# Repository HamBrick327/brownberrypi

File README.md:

# brownberrypi
my cyberdeck project and my first try at PCB design.

## note: the keyboard is not perfectly square, I did a dumb and only eyeballed it in KiCad, fix reccomended

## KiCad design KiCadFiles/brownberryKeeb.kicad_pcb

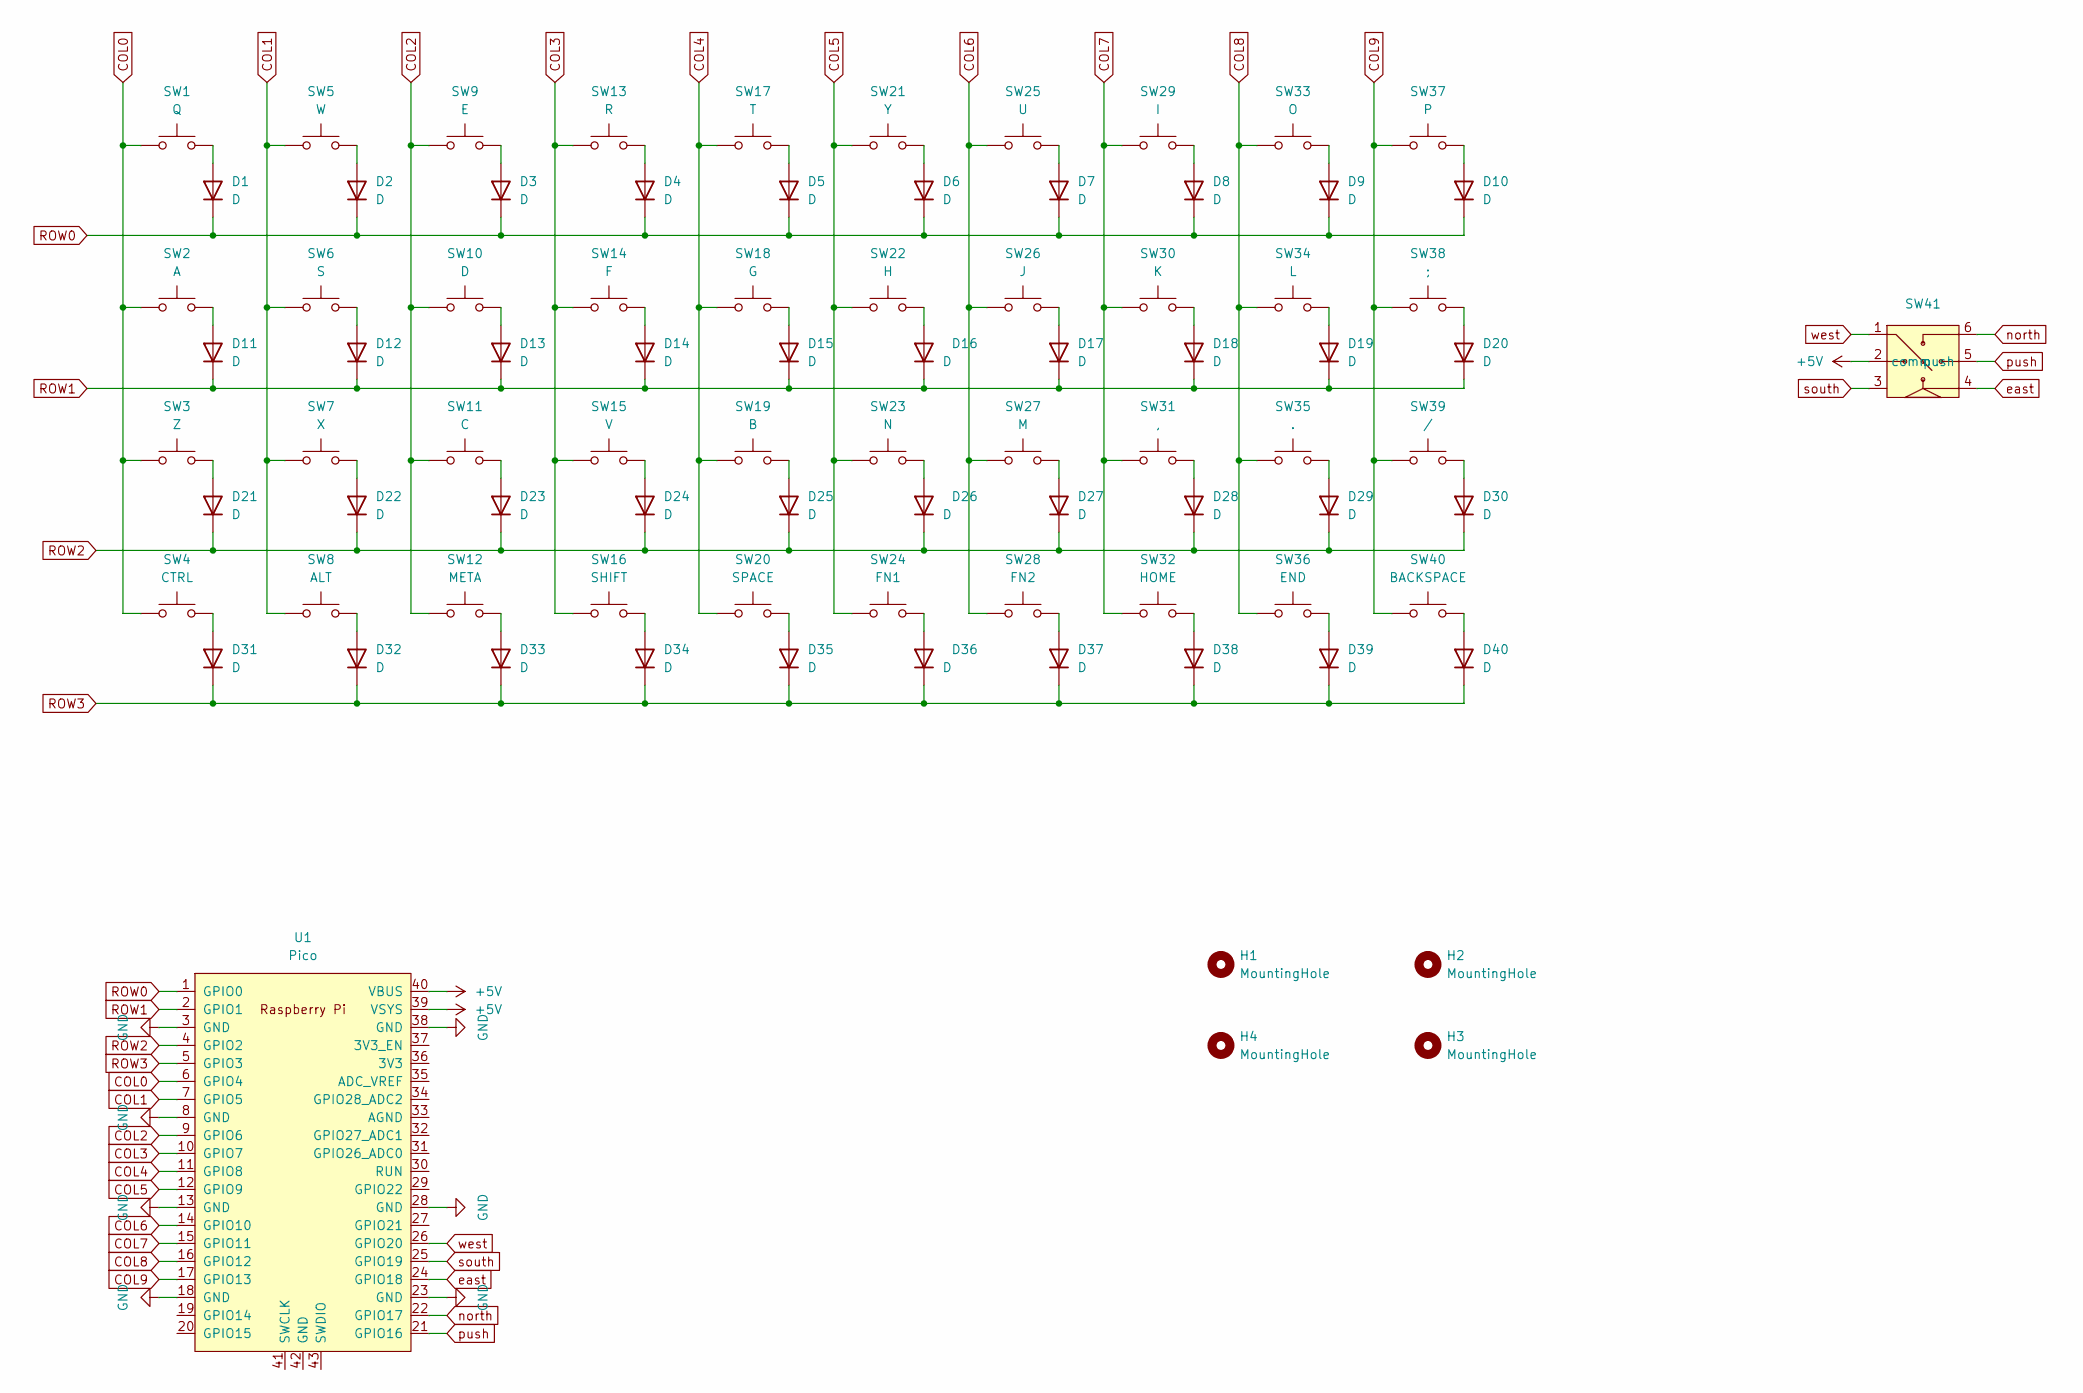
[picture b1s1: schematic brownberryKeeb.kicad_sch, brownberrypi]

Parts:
D1, D2, D3, D4, D5, D6, D7, D8, D9, D10, D11, D12, D13, D14, D15, D16, D17, D18, D19, D20, D21, D22, D23, D24, D25, D26, D27, D28, D29, D30, D31, D32, D33, D34, D35, D36, D37, D38, D39, D40: D; D_SOD-123
H1, H2, H3, H4: MountingHole; MountingHole_2.1mm
SW1: Q; SW_Push_1P1T_XKB_TS-1187A
SW2: A; SW_Push_1P1T_XKB_TS-1187A
SW3: Z; SW_Push_1P1T_XKB_TS-1187A
SW4: CTRL; SW_Push_1P1T_XKB_TS-1187A
SW5: W; SW_Push_1P1T_XKB_TS-1187A
SW6: S; SW_Push_1P1T_XKB_TS-1187A
SW7: X; SW_Push_1P1T_XKB_TS-1187A
SW8: ALT; SW_Push_1P1T_XKB_TS-1187A
SW9: E; SW_Push_1P1T_XKB_TS-1187A
SW10: D; SW_Push_1P1T_XKB_TS-1187A
SW11: C; SW_Push_1P1T_XKB_TS-1187A
SW12: META; SW_Push_1P1T_XKB_TS-1187A
SW13: R; SW_Push_1P1T_XKB_TS-1187A
SW14: F; SW_Push_1P1T_XKB_TS-1187A
SW15: V; SW_Push_1P1T_XKB_TS-1187A
SW16: SHIFT; SW_Push_1P1T_XKB_TS-1187A
SW17: T; SW_Push_1P1T_XKB_TS-1187A
SW18: G; SW_Push_1P1T_XKB_TS-1187A
SW19: B; SW_Push_1P1T_XKB_TS-1187A
SW20: SPACE; SW_Push_1P1T_XKB_TS-1187A
SW21: Y; SW_Push_1P1T_XKB_TS-1187A
SW22: H; SW_Push_1P1T_XKB_TS-1187A
SW23: N; SW_Push_1P1T_XKB_TS-1187A
SW24: FN1; SW_Push_1P1T_XKB_TS-1187A
SW25: U; SW_Push_1P1T_XKB_TS-1187A
SW26: J; SW_Push_1P1T_XKB_TS-1187A
SW27: M; SW_Push_1P1T_XKB_TS-1187A
SW28: FN2; SW_Push_1P1T_XKB_TS-1187A
SW29: I; SW_Push_1P1T_XKB_TS-1187A
SW30: K; SW_Push_1P1T_XKB_TS-1187A
SW31: ,; SW_Push_1P1T_XKB_TS-1187A
SW32: HOME; SW_Push_1P1T_XKB_TS-1187A
SW33: O; SW_Push_1P1T_XKB_TS-1187A
SW34: L; SW_Push_1P1T_XKB_TS-1187A
SW35: .; SW_Push_1P1T_XKB_TS-1187A
SW36: END; SW_Push_1P1T_XKB_TS-1187A
SW37: P; SW_Push_1P1T_XKB_TS-1187A
SW38: ;; SW_Push_1P1T_XKB_TS-1187A
SW39: /; SW_Push_1P1T_XKB_TS-1187A
SW40: BACKSPACE; SW_Push_1P1T_XKB_TS-1187A
SW41: 7x7x5_5-way_switch
U1: Pico; RaspberryPi_Pico_SMD

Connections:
+5V: SW41.2 (comm), U1.39 (VSYS), U1.40 (VBUS)
COL0: SW1.1, SW2.1, SW3.1, SW4.1, U1.6 (GPIO4)
COL1: SW5.1, SW6.1, SW7.1, SW8.1, U1.7 (GPIO5)
COL2: SW9.1, SW10.1, SW11.1, SW12.1, U1.9 (GPIO6)
COL3: SW13.1, SW14.1, SW15.1, SW16.1, U1.10 (GPIO7)
COL4: SW17.1, SW18.1, SW19.1, SW20.1, U1.11 (GPIO8)
COL5: SW21.1, SW22.1, SW23.1, SW24.1, U1.12 (GPIO9)
COL6: SW25.1, SW26.1, SW27.1, SW28.1, U1.14 (GPIO10)
COL7: SW29.1, SW30.1, SW31.1, SW32.1, U1.15 (GPIO11)
COL8: SW33.1, SW34.1, SW35.1, SW36.1, U1.16 (GPIO12)
COL9: SW37.1, SW38.1, SW39.1, SW40.1, U1.17 (GPIO13)
GND: U1.3 (GND), U1.8 (GND), U1.13 (GND), U1.18 (GND), U1.23 (GND), U1.28 (GND), U1.38 (GND)
unnamed: D1.2 (A), SW1.2
unnamed: D2.2 (A), SW5.2
unnamed: D3.2 (A), SW9.2
unnamed: D4.2 (A), SW13.2
unnamed: D5.2 (A), SW17.2
unnamed: D6.2 (A), SW21.2
unnamed: D7.2 (A), SW25.2
unnamed: D8.2 (A), SW29.2
unnamed: D9.2 (A), SW33.2
unnamed: D10.2 (A), SW37.2
unnamed: D11.2 (A), SW2.2
unnamed: D12.2 (A), SW6.2
unnamed: D13.2 (A), SW10.2
unnamed: D14.2 (A), SW14.2
unnamed: D15.2 (A), SW18.2
unnamed: D16.2 (A), SW22.2
unnamed: D17.2 (A), SW26.2
unnamed: D18.2 (A), SW30.2
unnamed: D19.2 (A), SW34.2
unnamed: D20.2 (A), SW38.2
unnamed: D21.2 (A), SW3.2
unnamed: D22.2 (A), SW7.2
unnamed: D23.2 (A), SW11.2
unnamed: D24.2 (A), SW15.2
unnamed: D25.2 (A), SW19.2
unnamed: D26.2 (A), SW23.2
unnamed: D27.2 (A), SW27.2
unnamed: D28.2 (A), SW31.2
unnamed: D29.2 (A), SW35.2
unnamed: D30.2 (A), SW39.2
unnamed: D31.2 (A), SW4.2
unnamed: D32.2 (A), SW8.2
unnamed: D33.2 (A), SW12.2
unnamed: D34.2 (A), SW16.2
unnamed: D35.2 (A), SW20.2
unnamed: D36.2 (A), SW24.2
unnamed: D37.2 (A), SW28.2
unnamed: D38.2 (A), SW32.2
unnamed: D39.2 (A), SW36.2
unnamed: D40.2 (A), SW40.2
ROW0: D1.1 (K), D2.1 (K), D3.1 (K), D4.1 (K), D5.1 (K), D6.1 (K), D7.1 (K), D8.1 (K), D9.1 (K), D10.1 (K), U1.1 (GPIO0)
ROW1: D11.1 (K), D12.1 (K), D13.1 (K), D14.1 (K), D15.1 (K), D16.1 (K), D17.1 (K), D18.1 (K), D19.1 (K), D20.1 (K), U1.2 (GPIO1)
ROW2: D21.1 (K), D22.1 (K), D23.1 (K), D24.1 (K), D25.1 (K), D26.1 (K), D27.1 (K), D28.1 (K), D29.1 (K), D30.1 (K), U1.4 (GPIO2)
ROW3: D31.1 (K), D32.1 (K), D33.1 (K), D34.1 (K), D35.1 (K), D36.1 (K), D37.1 (K), D38.1 (K), D39.1 (K), D40.1 (K), U1.5 (GPIO3)
east: SW41.4, U1.24 (GPIO18)
north: SW41.6, U1.22 (GPIO17)
push: SW41.5 (push), U1.21 (GPIO16)
south: SW41.3, U1.25 (GPIO19)
west: SW41.1, U1.26 (GPIO20)

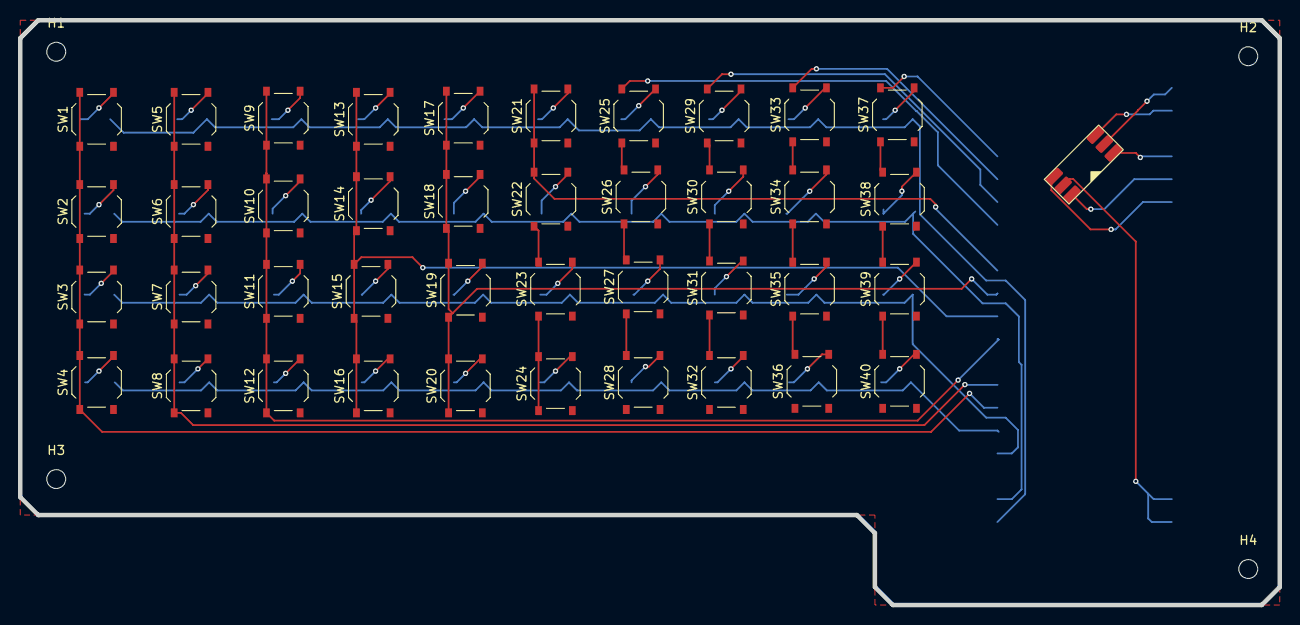
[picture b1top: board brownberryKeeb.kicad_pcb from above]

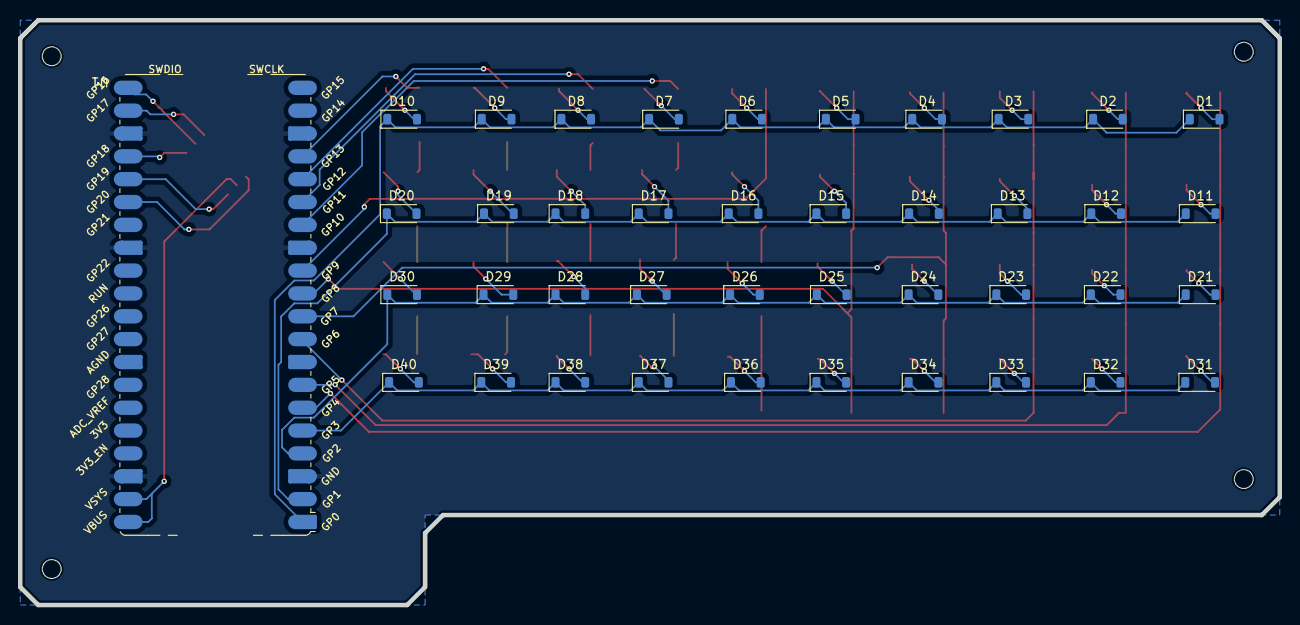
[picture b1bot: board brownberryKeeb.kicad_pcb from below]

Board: 2 copper layers, 140.0 x 65.0 mm, 86 parts (41 on the bottom side), 61 nets.

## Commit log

2025-04-23 Updated filestructure and added keeb frimware
2025-04-24 fixed PCB forgotten trace and added my homebrew footprints
2025-05-05 started the port to circuitpython, code is currently broken
2025-05-11 added some FreeCAD files, starting the case
2025-05-13 mode CAD, yay!
2025-05-16 updated the case, top half is done now. also made buttons
2025-05-16 ported I think the rest of keeb.py to circuitpython, still untested
2025-05-20 updated keeb.py
2025-05-21 code works... probably, currently at a bug that may be either hardware or software
